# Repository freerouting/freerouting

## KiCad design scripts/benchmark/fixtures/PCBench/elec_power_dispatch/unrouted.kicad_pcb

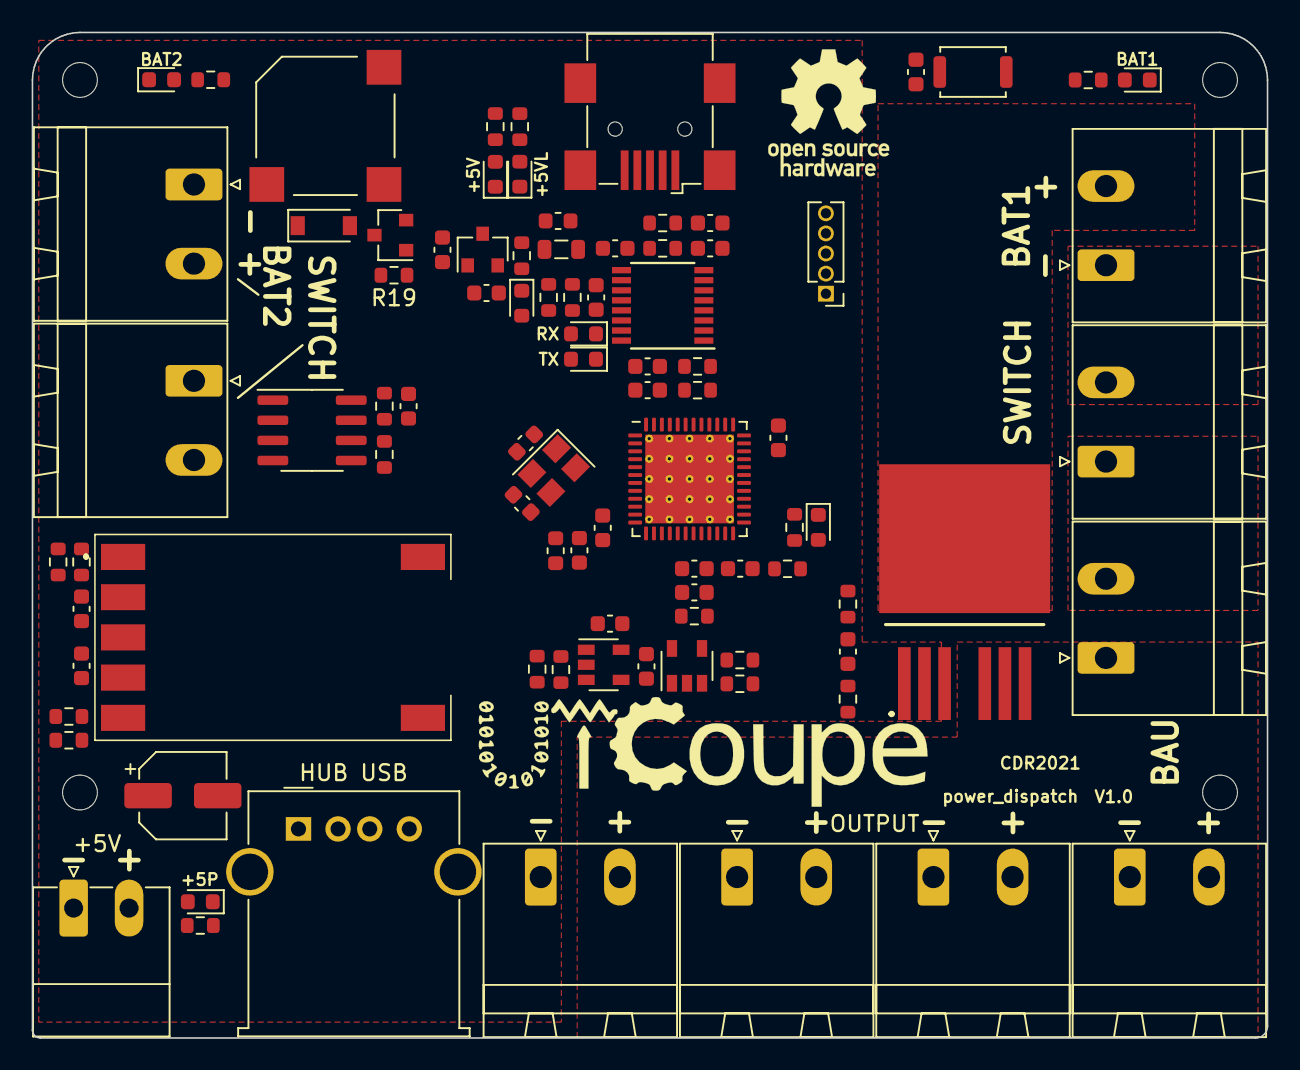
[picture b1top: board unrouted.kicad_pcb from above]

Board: 2 copper layers, 78.0 x 63.5 mm, 95 parts (0 on the bottom side), 57 nets, no tracks yet.

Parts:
BZ1: MLT-8530; MagneticBuzzer_Kobitone_254-EMB84Q-RO
C1, C4, C9, C13, C14, C15, C17, C18, C22, C24, C26: 100nF; C_0603_1608Metric
C2: 100uF/10V; CP_Elec_5x5.4
C3, C6, C12: 4u7; C_0603_1608Metric
C5, C7: 10uF; C_0603_1608Metric
C8: 220nF; C_0603_1608Metric
C10, C11: 12pF; C_0603_1608Metric
C16: 1u; C_0603_1608Metric
C19: 10nF; C_0603_1608Metric
C23, C25: 47pF; C_0603_1608Metric
D1, D2, D3, D4, D7, D9: red0603; LED_0603_1608Metric
D5, D6: blue0603; LED_0603_1608Metric
D8: 1N4148W; D_SOD-123
D10: green0603; LED_0603_1608Metric
F1: 100mA; Fuse_0603_1608Metric
FB1: 100 @ 100MHz; L_0805_2012Metric
H1, H2, H3, H4: MountingHole; MountingHole_2.2mm_M2
IC1: SRBH-06H1A1G; SRBH06H1A1G
IC2: BTS500251TADATMA2; IPB180N03S4L01
J1, J2, J3, J4, J5, J8, J9, J10, J11: Conn_01x02; PhoenixContact_MSTBA_2,5_2-G_1x02_P5.00mm_Horizontal
J6: USB_B_Mini; USB_Mini-B_Wuerth_65100516121_Horizontal
J7: Conn_01x05; PinHeader_1x05_P1.27mm_Vertical
J13: Conn_01x02; PhoenixContact_MC_1,5_2-G-3.5_1x02_P3.50mm_Horizontal
J15: USB_A; USB_A_Molex_67643_Horizontal
L1: 39nH; L_0603_1608Metric
LOGO1: Logo_Open_Hardware_Large; OSHW-Logo_7.5x8mm_SilkScreen
Q1: 2N7002E; SOT-23
R1, R10, R14, R24, R26: 3K3; R_0603_1608Metric
R2, R12: 4K7; R_0603_1608Metric
R3, R5, R6, R8, R25, R27, R28: 10K; R_0603_1608Metric
R4: 2K2; R_0603_1608Metric
R7, R9: 1K5; R_0603_1608Metric
R11, R13: 1K; R_0603_1608Metric
R15, R16: 27R; R_0603_1608Metric
R17, R20, R21: NC; R_0603_1608Metric
R18: 0R; R_0603_1608Metric
R19: 470R; R_0603_1608Metric
R22, R23: 270R; R_0603_1608Metric
SW1: SKRKAEE020; SW_Push_SPST_NO_Alps_SKRK
U1, U8: MCP6L01x-xOT; SOT-23-5
U2: STM32F411CEUx; QFN-48-1EP_7x7mm_P0.5mm_EP5.6x5.6mm_ThermalVias
U3: FT230XS; SSOP-16_3.9x4.9mm_P0.635mm
U4: ACS722xLCTR-10AB; SOIC-8_3.9x4.9mm_P1.27mm
U5: XC6206P332MR; SOT-23
Y1: 1C208000BC0K 8MHz; Crystal_SMD_3225-4Pin_3.2x2.5mm

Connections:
+3.3VA: C4.1, C9.1, C16.2, C17.2, C18.1, L1.2, R17.1, U1.5, U2.9, U4.8, U8.5
+3V3: C7.1, C12.2, C13.2, C14.2, C22.2, D7.2, L1.1, R20.2, R21.1, U2.24, U2.36, U2.48, U5.2
+5V: C5.1, C24.1, FB1.1, R24.1, U3.12, U5.3
+5VL: C3.1, F1.2, J6.1, R1.1
+5VP: BZ1.1, C2.1, C26.1, D3.2, D8.1, IC1.4, J13.2, J15.1
+12P: IC2.5, IC2.6, IC2.7, J8.2, J9.2, J10.2, J11.2
+12V: C1.1, IC1.2, R27.1, U4.3, U4.4
+12VA: J1.2, R3.1, R6.1, U4.1, U4.2
+BATT: IC2.4, J3.2, R5.1, R8.1
/TRIM: IC1.5, R10.2
BOOT0: R20.1, R25.2, U2.44
BUZZER: R19.1, U2.46
CBUS1: D5.1, U3.14
CBUS2: D6.1, U3.7
GND: C1.2, C2.2, C3.2, C4.2, C5.2, C6.2, C7.2, C8.2, C9.2, C10.1, C11.2, C12.1, C13.1, C14.1, C15.2, C16.1, C17.1, C18.2, C19.2, C22.1, C23.2, C24.2, C25.2, C26.2, D1.1, D2.1, D9.1, D10.1, IC1.3, IC2.1, J2.1, J5.1, J6.5, J7.2, J8.1, J9.1, J10.1, J11.1, J13.1, J15.4, Q1.2, R4.1, R7.2, R11.1, R13.1, R14.2, R18.2, R25.1, R28.2, SW1.2, U1.2, U2.8, U2.23, U2.35, U2.47, U2.49, U3.5, U3.13, U4.5, U5.1, U8.2, Y1.2, Y1.4
GNDBATT: J3.1, J4.2
HSE_IN: C10.2, U2.5, Y1.1
HSE_OUT: C11.1, U2.6, Y1.3
LED0: R26.1, U2.26
NRST: C15.1, J7.4, SW1.1, U2.7
unnamed: BZ1.2, D8.2, Q1.3
unnamed: C6.1, U2.22
unnamed: C8.1, IC2.2, R12.1
unnamed: C23.1, R15.2, U3.9
unnamed: C25.1, R16.2, U3.8
unnamed: D1.2, R1.2
unnamed: D2.2, R3.2
unnamed: D3.1, R4.2
unnamed: D4.1, J4.1, J5.2, R9.2
unnamed: D4.2, R5.2
unnamed: D5.2, R22.1
unnamed: D6.2, R23.1
unnamed: D7.1, R14.1
unnamed: D9.2, R24.2
unnamed: D10.2, R26.2
unnamed: F1.1, FB1.2
unnamed: IC1.1, R27.2, R28.1
unnamed: IC2.3, R2.1, R13.2
unnamed: J1.1, J2.2
unnamed: Q1.1, R19.2
unnamed: R6.2, R7.1, U1.3
unnamed: R8.2, R9.1, U8.3
unnamed: R10.1, R11.2
unnamed: R17.2, R18.1, U4.6
PWRCMD: R12.2, R21.2, U2.25
SWCLK: J7.1, U2.37
SWDIO: J7.3, U2.34
SWO: J7.5, U2.39
UART_RX: U2.31, U3.1
UART_TX: U2.30, U3.4
USB_D+: J6.3, R16.1
USB_D-: J6.2, R15.1
VCCIO: R22.2, R23.2, U3.3, U3.10, U3.11
VILOGIC: U2.13, U4.7
VIPOWER: C19.1, R2.2, U2.16
VVLOGIC: U1.1, U1.4, U2.14
VVPOWER: U2.15, U8.1, U8.4

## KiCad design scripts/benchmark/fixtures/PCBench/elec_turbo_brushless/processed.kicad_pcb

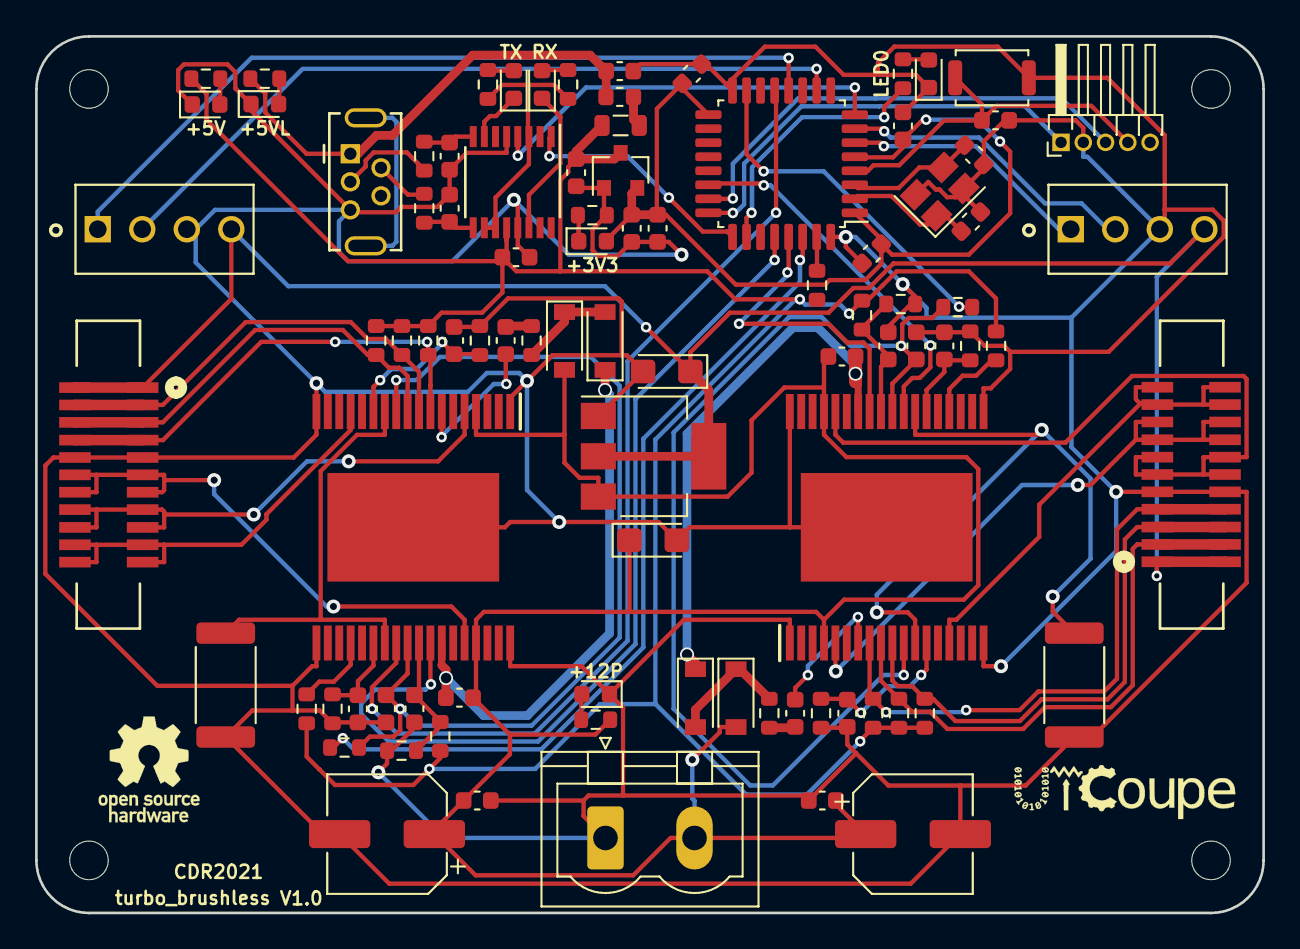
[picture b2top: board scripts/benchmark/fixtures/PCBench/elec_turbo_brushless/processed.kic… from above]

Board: 2 copper layers, 70.0 x 50.0 mm, 96 parts (0 on the bottom side), 72 nets.

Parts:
C1, C11: 4u7; C_0603_1608Metric
C2, C5: 10uF; C_0603_1608Metric
C3, C4: 12pF; C_0603_1608Metric
C6: 10uF; CP_EIA-3216-18_Kemet-A
C7: 22uF; CP_EIA-3216-18_Kemet-A
C8, C10: 47pF; C_0603_1608Metric
C9, C12, C13, C18, C22, C25, C31: 100nF; C_0603_1608Metric
C14, C26: 220nF; C_0603_1608Metric
C15, C19, C28, C29: 10nF; C_0603_1608Metric
C16, C23: 1nF; C_0603_1608Metric
C17, C24: 100uF; CP_Elec_6.3x7.7
C20, C30: 5.6nF; C_0603_1608Metric
C21, C27: 47nF; C_0603_1608Metric
D1, D2, D5, D11: red0603; LED_0603_1608Metric
D3, D4: blue0603; LED_0603_1608Metric
D6, D7, D9, D10: 1N4148; D_SOD-123
D8: green0603; LED_0603_1608Metric
F1: 100mA; Fuse_0603_1608Metric
FB1: 100 @ 100MHz; L_0805_2012Metric
H1, H2, H3, H4: MountingHole; MountingHole_2.2mm_M2
IC1, IC2: L6235PD; SOP65P1420X360-37N
J1: USB_B_Mini; USB_Mini-B_Tensility_54-00023_Vertical
J2: Conn_01x02; PhoenixContact_MSTBVA_2,5_2-G-5,08_1x02_P5.08mm_Vertical
J3, J5: Conn_01x11; MOLEX_52610-0571_FPC_01x11_p1.0mm
J4: Conn_01x05; PinHeader_1x05_P1.27mm_Horizontal
J6, J7: Conn_01x04; Headers-Wire_Housings_HEADER_4POS_HE14
LOGO1: Logo_Open_Hardware_Large; OSHW-Logo_5.7x6mm_SilkScreen
R1, R2, R3, R8: 3K3; R_0603_1608Metric
R4, R5: 27R; R_0603_1608Metric
R6, R7: 270R; R_0603_1608Metric
R9, R11, R12, R13, R18, R20, R21, R22, R24, R28, R31, R32: 10K; R_0603_1608Metric
R10, R27: 100; R_0603_1608Metric
R14, R23: 33K; R_0603_1608Metric
R15, R26: 47K; R_0603_1608Metric
R16, R30: 100K; R_0603_1608Metric
R17, R25: N/A; R_0603_1608Metric
R19, R29: 0.25/1W 1%; R_2512_6332Metric
SW1: SKRKAEE020; SW_Push_SPST_NO_Alps_SKRK
U1: STM32F303K8Tx; LQFP-32_7x7mm_P0.8mm
U2: XC6206P332MR; SOT-23
U3: FT230XS; SSOP-16_3.9x4.9mm_P0.635mm
U4: AMS1117-5.0; SOT-223-3_TabPin2
Y1: 1C208000BC0K 8MHz; Crystal_SMD_3225-4Pin_3.2x2.5mm

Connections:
+3V3: C5.1, C11.1, C12.1, C13.1, C31.1, D2.2, U1.1, U1.5, U1.17, U2.2
+5V: C2.1, C9.1, FB1.1, R8.1, R9.1, R11.2, R12.2, R13.2, R18.1, R20.2, R21.2, R22.2, R24.1, R28.1, U2.3, U3.12
+5VL: C1.1, F1.2, J1.1, R1.1
+5VP: C7.1, J3.1, J5.1, J6.4, J7.4, U4.2
+12P: C6.1, C14.1, C17.1, C18.1, C24.1, C25.1, C26.1, D6.2, D9.2, IC1.4, IC1.33, IC2.4, IC2.33, J2.2, R32.1, U4.3
/DIAG_1: C20.1, IC1.11, IC1.27, R16.1
/DIAG_2: C30.1, IC2.11, IC2.27, R30.1
/VBOOT_1: C14.2, D7.1, IC1.30
/VBOOT_2: C26.2, D10.1, IC2.30
/VCP_1: C15.1, IC1.7
/VCP_2: C29.1, IC2.7
BOOT0: R31.1, U1.31
BRAKE_1: IC1.29, U1.28
BRAKE_2: IC2.29, U1.29
CBUS1: D3.1, U3.14
CBUS2: D4.1, U3.7
ENABLE_1: R16.2, U1.30
ENABLE_2: R30.2, U1.15
ENC_A_1: J7.1, U1.12
ENC_A_2: J6.1, U1.6
ENC_B_1: J7.2, U1.10
ENC_B_2: J6.2, U1.7
FWD_REV_1: IC1.26, U1.13
FWD_REV_2: IC2.26, U1.22
GND: C1.2, C2.2, C3.2, C4.2, C5.2, C6.2, C7.2, C8.2, C9.2, C10.2, C11.2, C12.2, C13.2, C16.1, C17.2, C18.2, C19.1, C20.2, C21.2, C22.2, C23.1, C24.2, C25.2, C27.2, C28.1, C30.2, C31.2, D1.1, D5.1, D8.1, D11.1, IC1.1, IC1.18, IC1.19, IC1.36, IC1.37, IC2.1, IC2.18, IC2.19, IC2.36, IC2.37, J1.5, J2.1, J3.5, J4.2, J5.5, J6.3, J7.3, R3.2, R14.2, R15.2, R17.2, R19.2, R23.2, R25.2, R26.2, R29.2, SW1.2, U1.16, U1.32, U2.1, U3.5, U3.13, U4.1, Y1.2, Y1.4
H1_1: IC1.10, J3.3, R13.1
H1_2: IC2.10, J5.3, R22.1
H2_1: IC1.8, J3.4, R11.1
H2_2: IC2.8, J5.4, R20.1
H3_1: IC1.9, J3.2, R12.1
H3_2: IC2.9, J5.2, R21.1
HSE_IN: C3.1, U1.2, Y1.1
HSE_OUT: C4.1, U1.3, Y1.3
LED0: R2.1, U1.26
NRST: C22.1, J4.4, SW1.1, U1.4
unnamed: C8.1, R4.2, U3.9
unnamed: C10.1, R5.2, U3.8
unnamed: C15.2, R10.1
unnamed: C16.2, IC1.13, R14.1
unnamed: C19.2, IC1.24, R15.1
unnamed: C21.1, IC1.28, R9.2, R17.1
unnamed: C23.2, IC2.13, R23.1
unnamed: C27.1, IC2.28, R24.2, R25.1
unnamed: C28.2, IC2.24, R26.1
unnamed: C29.2, R27.1
unnamed: D1.2, R1.2
unnamed: D2.1, R3.1
unnamed: D3.2, R6.1
unnamed: D4.2, R7.1
unnamed: D5.2, R8.2
unnamed: D6.1, D7.2, R10.2
unnamed: D8.2, R2.2
unnamed: D9.1, D10.2, R27.2
unnamed: D11.2, R32.2
unnamed: F1.1, FB1.2
OUT1_1: IC1.15, J3.10, J3.11
OUT1_2: IC2.15, J5.10, J5.11
OUT2_1: IC1.5, J3.8, J3.9
OUT2_2: IC2.5, J5.8, J5.9
OUT3_1: IC1.32, J3.6, J3.7
OUT3_2: IC2.32, J5.6, J5.7
SENSE_1: IC1.12, IC1.25, R19.1
SENSE_2: IC2.12, IC2.25, R29.1
SWCLK: J4.1, U1.24
SWDIO: J4.3, U1.23
TACHO_1: IC1.22, R18.2
TACHO_2: IC2.22, R28.2
UART_RX: U1.25, U3.1
UART_TX: U1.8, U3.4
USB_D+: J1.3, R5.1
USB_D-: J1.2, R4.1
VCCIO: R6.2, R7.2, U3.3, U3.10, U3.11

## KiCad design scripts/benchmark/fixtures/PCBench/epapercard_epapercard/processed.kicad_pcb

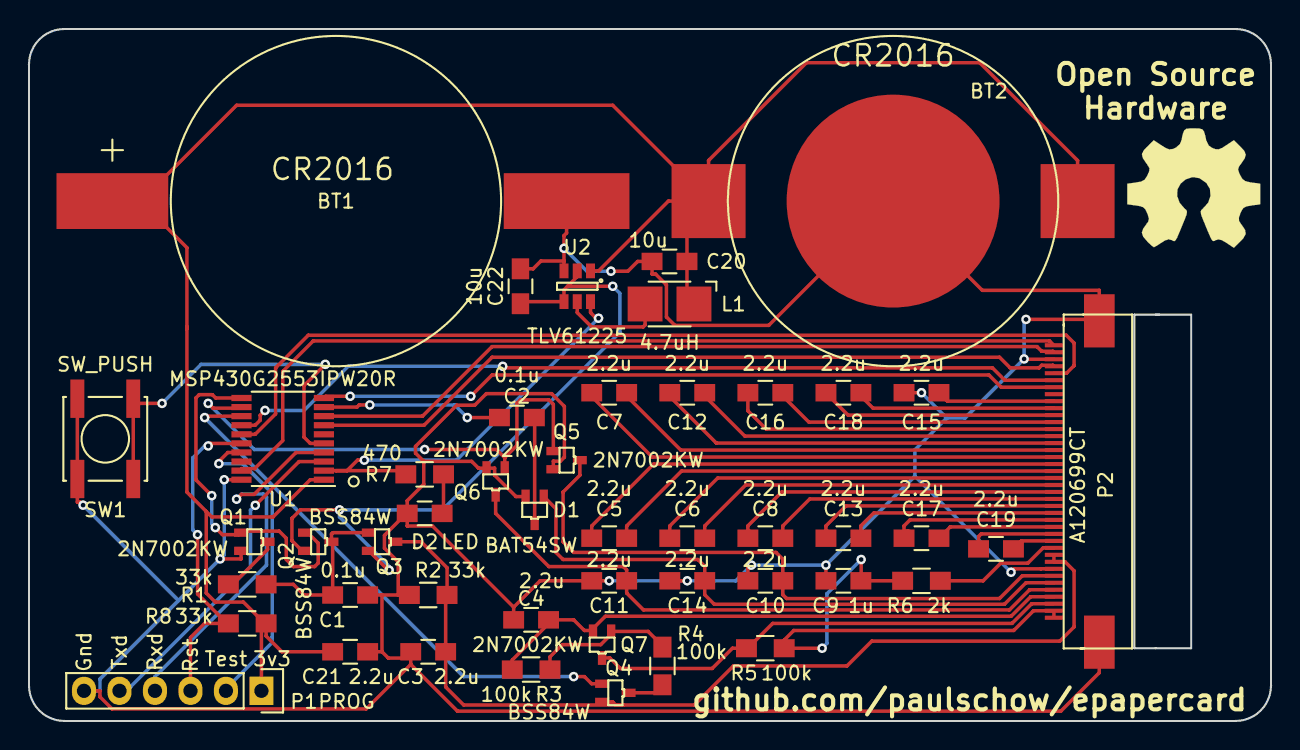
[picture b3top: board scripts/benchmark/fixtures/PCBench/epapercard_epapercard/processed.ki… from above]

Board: 2 copper layers, 88.9 x 49.5 mm, 47 parts (0 on the bottom side), 55 nets.

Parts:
BT1: CR2016; CR2016sm-F2N
BT2: CR2016; CR2032sm
C1, C2: 0.1u; C_0805_HandSoldering
C3, C4, C5, C6, C7, C8, C10, C11, C12, C13, C14, C15, C16, C17, C18, C19, C21: 2.2u; C_0805_HandSoldering
C9: 1u; C_0805_HandSoldering
C20, C22: 10u; C_0805_HandSoldering
D1: BAT54SW; SOT-323
D2: LED; C_0805_HandSoldering
L1: 4.7uH; Inductor_1212
P1: PROG; Pin_Header_Straight_1x06
P2: A120699CT
Q1, Q5, Q6, Q7: 2N7002KW; SOT-323
Q2, Q3, Q4: BSS84W; SOT-323
R1, R2, R8: 33k; R_0805_HandSoldering
R3, R4, R5: 100k; R_0805_HandSoldering
R6: 2k; R_0805_HandSoldering
R7: 470; R_0805_HandSoldering
SW1: SW_PUSH; SW_SPST_EVPBF
U1: MSP430G2553IPW20R; TSSOP-20_4.4x6.5mm_Pitch0.65mm
U2: TLV61225; SOT-23-6

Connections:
+3.3VP: C3.2, P2.31, P2.32, Q3.3, Q4.2, R2.2
+3V3: BT1.1, BT2.1, C20.2, C21.2, L1.1, P1.1, R8.2, U1.1, U2.1
/BORDER: P2.38, Q7.3, R5.2
/EPD_CS: P2.1, U1.19
/RESET: P2.7, U1.10
/VCOM: C9.1, P2.39, P2.40, R5.1, R6.2
/VDH: C11.1, P2.36, Q6.3
/VDL: C4.1, P2.37, Q7.2, R3.2
/VGH: C10.1, P2.34, Q5.3
/VGL: C14.1, D1.1, P2.35
/Vboost: C22.2, Q2.2, Q3.2, U2.2, U2.4
/button: SW1.1, U1.5
/led: R7.2, U1.2, U2.6
/rst: P1.3, R8.1, U1.16
/rxd: P1.4, U1.4
/test: P1.2, U1.17
/txd: P1.5, U1.3
BORDER_CONTROL: Q4.1, U1.13
BUSY: P2.2, U1.8
DISCHARGE: Q5.1, Q6.1, U1.12
GND: BT1.2, BT2.2, C1.1, C3.1, C4.2, C9.2, C10.2, C11.2, C14.2, C15.2, C20.1, C21.1, C22.1, D1.2, D2.1, P1.6, P2.3, P2.33, P2.41, Q1.2, Q5.2, Q6.2, R2.1, SW1.2, U1.20, U2.3
unnamed: C1.2, Q2.3, Q3.1, R1.1
unnamed: C2.1, D1.3
unnamed: C5.1, P2.18
unnamed: C5.2, P2.19
unnamed: C6.1, P2.20
unnamed: C6.2, P2.21
unnamed: C7.1, P2.16
unnamed: C7.2, P2.17
unnamed: C8.1, P2.22
unnamed: C8.2, P2.23
unnamed: C12.1, P2.14
unnamed: C12.2, P2.15
unnamed: C13.1, P2.24
unnamed: C13.2, P2.25
unnamed: C15.1, P2.9
unnamed: C16.1, P2.12
unnamed: C16.2, P2.13
unnamed: C17.1, P2.26
unnamed: C17.2, P2.27
unnamed: C18.1, P2.10
unnamed: C18.2, P2.11
unnamed: C19.1, P2.28
unnamed: C19.2, P2.29
unnamed: D2.2, R7.1
unnamed: L1.2, U2.5
unnamed: P2.30, R6.1
unnamed: Q1.3, R1.2
unnamed: Q4.3, R4.1
unnamed: Q7.1, R3.1, R4.2
PANEL_ON: Q1.1, Q2.1, U1.11
PWM: C2.2, U1.9
SPI_CLK: P2.4, U1.7
SPI_MISO: P2.6, U1.14
SPI_MOSI: P2.5, U1.15

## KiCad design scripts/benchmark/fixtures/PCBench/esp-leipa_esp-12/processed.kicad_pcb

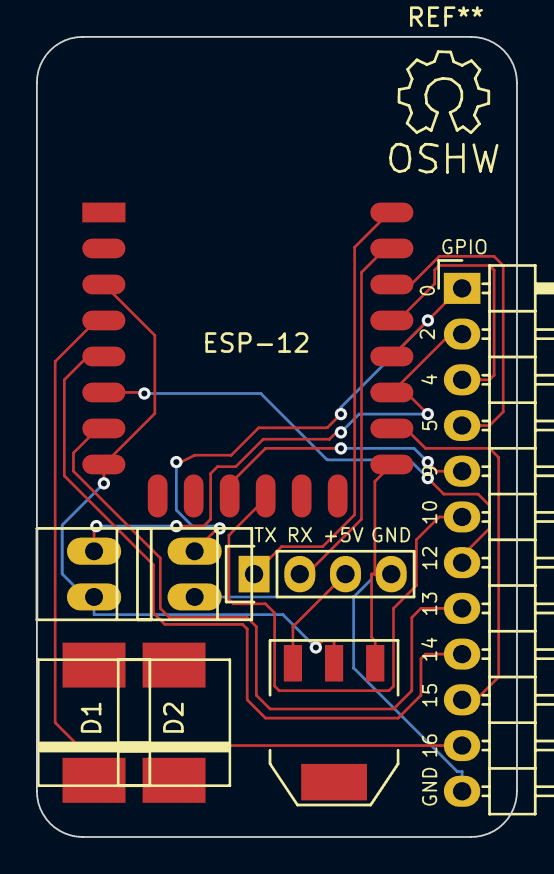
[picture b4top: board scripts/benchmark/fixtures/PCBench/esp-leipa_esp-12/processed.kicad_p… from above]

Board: 2 copper layers, 26.7 x 44.4 mm, 8 parts (0 on the bottom side), 16 nets.

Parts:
D1, D2: D; DIODE_DO214AB-SMC
ESP-12: ESP-12E
F1, F2: JUMPER; PINHEAD1-2
P1: CONN_01X12; Pin_Header_Angled_1x12
P2: UART; Pin_Header_Straight_1x04
U1: LD1117S33TR; SOT-223

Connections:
+5V: P2.3, U1.3
EN: ESP-12.3, ESP-12.8, F2.2, U1.2
GND: ESP-12.15, F1.2, P1.12, P2.4, U1.1
GPIO0: ESP-12.18, F1.1, P1.1
GPIO2: ESP-12.17, F2.1, P1.2
GPIO4: ESP-12.19, P1.3
GPIO5: ESP-12.20, P1.4
GPIO9: ESP-12.11, P1.5
GPIO10: ESP-12.12, P1.6
GPIO12: ESP-12.6, P1.7
GPIO13: ESP-12.7, P1.8
GPIO14: ESP-12.5, P1.9
GPIO15: ESP-12.16, P1.10
GPIO16: ESP-12.4, P1.11
RXD0: ESP-12.21, P2.2
TXD0: ESP-12.22, P2.1
